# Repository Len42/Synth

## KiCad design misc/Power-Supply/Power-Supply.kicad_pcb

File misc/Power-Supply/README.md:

# Eurorack Power Supply

This is the power supply that I made for my Eurorack modular system.

[See here for more info, photos, etc.](https://lenp.net/synth/power-supply/)

### Specs

Input: Requires between 9 V and 36 V DC, 35W (from a power brick / wall wart / laptop charger)

Output: +12 V, -12 V (1 A each), +5 V (500 mA)

### Notes

I used an old laptop charger as the AC-DC converter (power brick) so I didn't have to mess around with mains voltage. The required Eurorack voltages (+12 V, -12 V, +5 V) are supplied by switching DC-DC converters. The outputs are isolated from the input.

There are two 16-pin Eurorack power connectors; you'll want a busboard or flying-bus cable to feed multiple modules.

The power supply is assembled on a stripboard PCB. I have provided a layout diagram.

Please note that I am a hobbyist, not a trained electronics engineer. No guarantees!

### Software Used

[KiCad](https://www.kicad.org/) 6.0.10

<hr /><br />© 2022 Len Popp CC BY<br />This work is licensed under a <a rel="license" href="http://creativecommons.org/licenses/by/4.0/">Creative Commons Attribution 4.0 International License</a>.

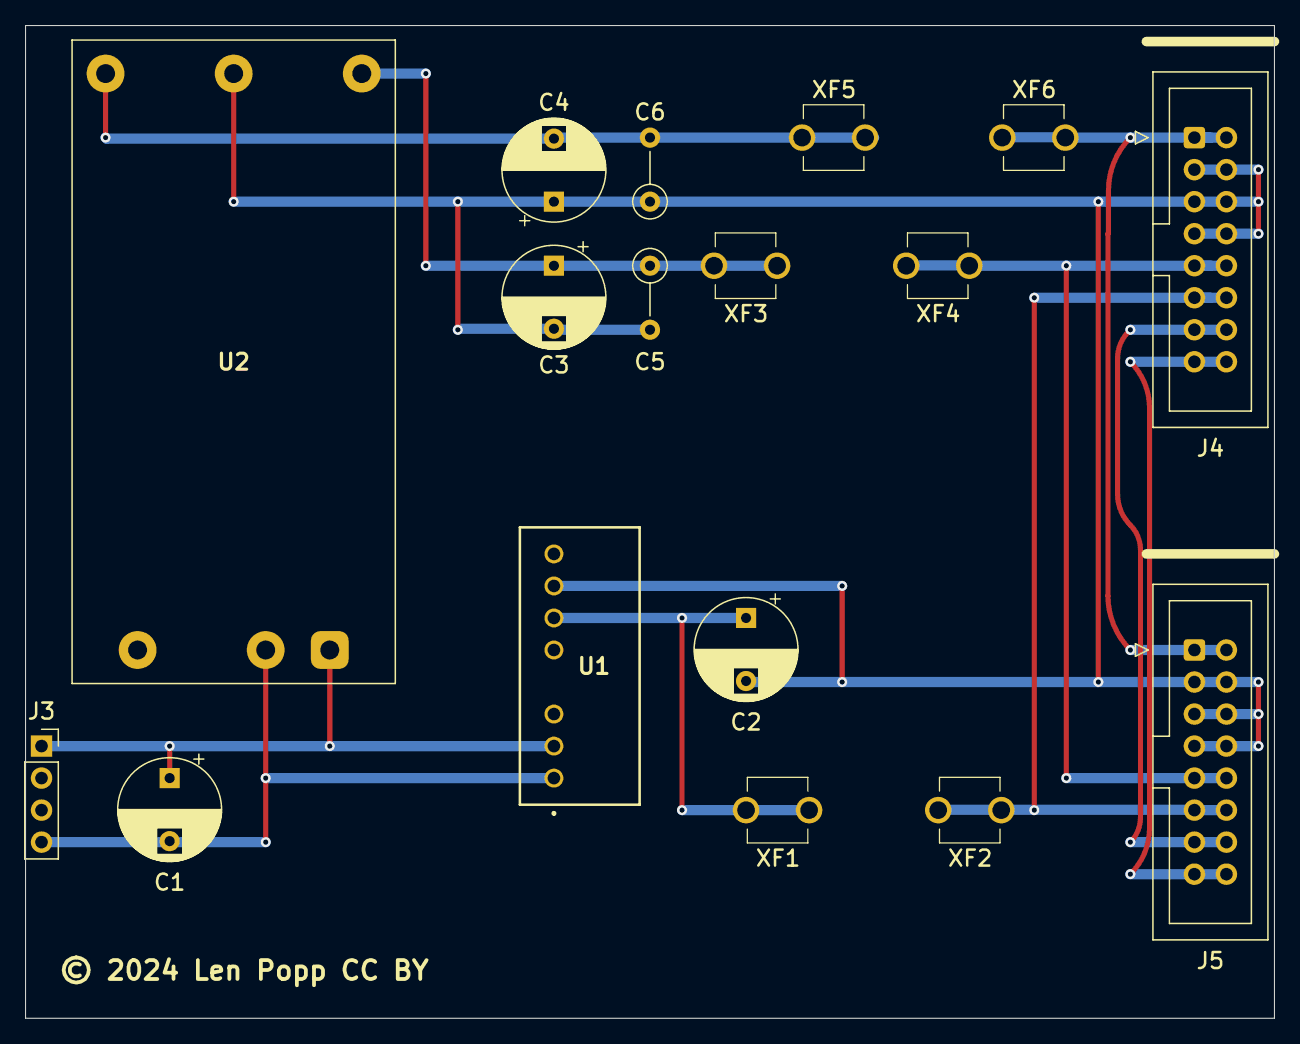
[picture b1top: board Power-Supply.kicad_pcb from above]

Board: 2 copper layers, 99.1 x 78.7 mm, 17 parts (0 on the bottom side), 11 nets.

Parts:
C1, C3, C4: 220U; CP_Radial_D8.0mm_P5.00mm
C2: 22U; CP_Radial_D8.0mm_P5.00mm
C5, C6: 100N; SB_Gen_2
J3: HDR_F; PinSocket_1x04_P2.54mm_Vertical
J4, J5: Conn_Eurorack_Pwr_16; IDC-Header-Eurorack-16-TH
U1: PRM3W-E12-S5-S; Converter_DCDC_CUI_PRM3W
U2: PYBE30-Q24-D12; Converter_DCDC_CUI_PYBE30
XF1, XF2, XF3, XF4, XF5, XF6: CLIP; FuseClip_D5mm_P5mm_52000001009

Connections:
+5V: J4.11 (+5V), J4.12, J5.11 (+5V), J5.12, XF2.1
+12V: J4.9 (+12V), J4.10, J5.9 (+12V), J5.10, XF4.1
-12V: J4.1 (-12V), J4.2, J5.1 (-12V), J5.2, XF6.1
GND: C2.2, C3.2, C4.1, C5.2, C6.1, J4.3 (GND), J4.4, J4.5 (GND), J4.6, J4.7 (GND), J4.8, J5.3 (GND), J5.4, J5.5 (GND), J5.6, J5.7 (GND), J5.8, U1.7 (0V), U2.5 (0V)
unnamed: C1.1, J3.1, U1.2 (+VIN), U2.1 (+VIN)
unnamed: C1.2, J3.4, U1.1 (-VIN), U2.2 (-VIN)
unnamed: C2.1, U1.6 (+VOUT), XF1.1
unnamed: C3.1, C5.1, U2.6 (+VOUT), XF3.1
unnamed: C4.2, C6.2, U2.4 (-VOUT), XF5.1
unnamed: J4.13 (CV), J4.14, J5.13 (CV), J5.14
unnamed: J4.15 (GATE), J4.16, J5.15 (GATE), J5.16

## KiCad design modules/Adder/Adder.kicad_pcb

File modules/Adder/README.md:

# Unity-Gain Mixer / Precision Adder

## 4HP Eurorack Module

### Features
- Two 3:1 mixing channels usable for CV or audio signals
- All inputs are mixed equally, _i.e._ added together
- Blinking lights show when an output is active and whether it's a CV or audio signal
- _Optional:_ A high-precision CV adder, if precision components are used

### Notes
To make a high-precision adder (_e.g._ to add pitch CVs without going out of tune):
- Use precision resistors (0.1% tolerance) for all 10kΩ resistors
- Use precision op-amps for U1, U2, and U4 (but not U3, all it does is blink an LED)

Note that some precision op-amps have low bandwidth or slew rate, which can be a problem for mixing audio signals. For example, I found that the LT1013/4 is good for accurately adding pitch CVs but causes distortion of audio-frequency signals. A possible compromise is to use precision resistors and regular op-amps (TL07x).

PCB layouts are provided in KiCad and gerber formats. A PCB layout for a drilled front panel (with no labels) is also included.

The PCBs that I used can be ordered from OSH Park. The designs are here:
- [Controls board](https://oshpark.com/shared_projects/eqKM6fyu)
- [Main board](https://oshpark.com/shared_projects/4ohHbdpn)
- [Front panel](https://oshpark.com/shared_projects/z20NA99Y)

Please note that I am a hobbyist, not a trained electronics engineer. No guarantees!

### Software Used

* [KiCad](https://www.kicad.org/) 6.0.8

<hr /><div><div style="float:left; padding-right:10px;"></div><div style="xfloat:left; padding-left:10px;"><br />© 2022 Len Popp CC BY<br />This work is licensed under a <a rel="license" href="http://creativecommons.org/licenses/by/4.0/">Creative Commons Attribution 4.0 International License</a>.</div></div>

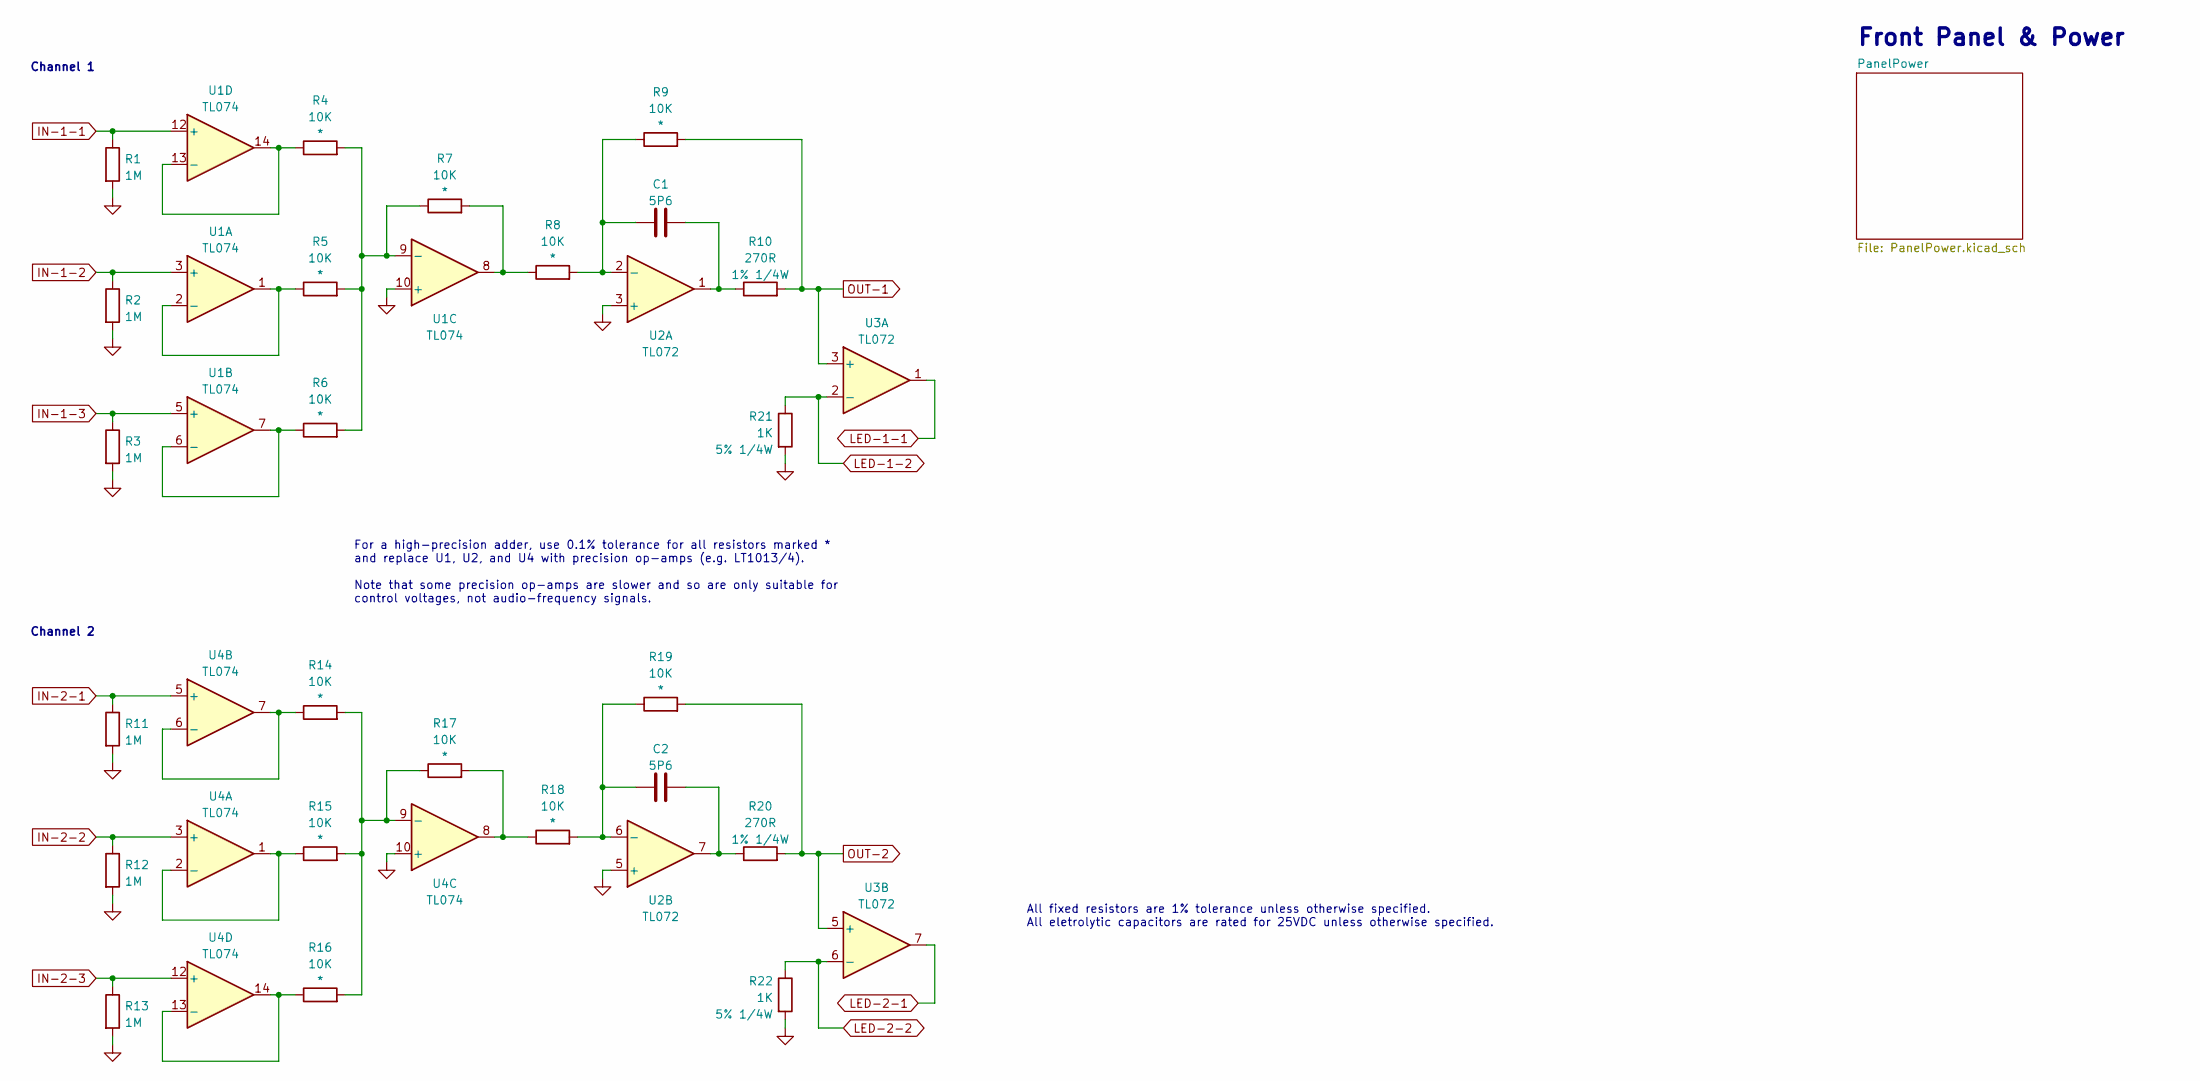
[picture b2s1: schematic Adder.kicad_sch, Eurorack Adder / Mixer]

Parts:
C1, C2: 5P6; C_Disc_D5.0mm_W2.5mm_P2.50mm; ManufacturerPartNum C315C569D1G5TA
R1, R2, R3, R11, R12, R13: 1M; R_Axial_DIN0207_L6.3mm_D2.5mm_P7.62mm_Horizontal; ManufacturerPartNum MFR-12FTF52-1M
R4, R5, R6, R7, R8, R9, R14, R15, R16, R17, R18, R19: 10K; R_Axial_DIN0207_L6.3mm_D2.5mm_P10.16mm_Horizontal; ManufacturerPartNum MFR-12FTF52-10K
R10, R20: 270R; R_Axial_DIN0207_L6.3mm_D2.5mm_P10.16mm_Horizontal; ManufacturerPartNum MFR-25FRF52-270R
R21, R22: 1K; R_Axial_DIN0207_L6.3mm_D2.5mm_P10.16mm_Horizontal; ManufacturerPartNum CCF071K00JKE36
U1, U4: TL074; DIP-14_W7.62mm; ManufacturerPartNum TL074BCN
U2, U3: TL072; DIP-8_W7.62mm; ManufacturerPartNum TL072BCP

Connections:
GND: R1.2, R2.2, R3.2, R11.2, R12.2, R13.2, R21.2, R22.2, U1.10 (+), U2.3 (+), U2.5 (+), U4.10 (+); also elsewhere on the board
IN-1-1: R1.1, U1.12 (+); also elsewhere on the board
IN-1-2: R2.1, U1.3 (+); also elsewhere on the board
IN-1-3: R3.1, U1.5 (+); also elsewhere on the board
IN-2-1: R11.1, U4.5 (+); also elsewhere on the board
IN-2-2: R12.1, U4.3 (+); also elsewhere on the board
IN-2-3: R13.1, U4.12 (+); also elsewhere on the board
LED-1-1: U3.1; also elsewhere on the board
LED-1-2: R21.1, U3.2 (-); also elsewhere on the board
LED-2-1: U3.7; also elsewhere on the board
LED-2-2: R22.1, U3.6 (-); also elsewhere on the board
unnamed: C1.1, R8.2, R9.1, U2.2 (-)
unnamed: C1.2, R10.1, U2.1
unnamed: C2.1, R18.2, R19.1, U2.6 (-)
unnamed: C2.2, R20.1, U2.7
unnamed: R4.1, U1.13 (-), U1.14
unnamed: R4.2, R5.2, R6.2, R7.1, U1.9 (-)
unnamed: R5.1, U1.1, U1.2 (-)
unnamed: R6.1, U1.6 (-), U1.7
unnamed: R7.2, R8.1, U1.8
unnamed: R14.1, U4.6 (-), U4.7
unnamed: R14.2, R15.2, R16.2, R17.1, U4.9 (-)
unnamed: R15.1, U4.1, U4.2 (-)
unnamed: R16.1, U4.13 (-), U4.14
unnamed: R17.2, R18.1, U4.8
OUT-1: R9.2, R10.2, U3.3 (+); also elsewhere on the board
OUT-2: R19.2, R20.2, U3.5 (+); also elsewhere on the board

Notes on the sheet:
All fixed resistors are 1% tolerance unless otherwise specified. All eletrolytic capacitors are rated for 25VDC unless otherwise specified.
For a high-precision adder, use 0.1% tolerance for all resistors marked * and replace U1, U2, and U4 with precision op-amps (e.g. LT1013/4). Note that some precision op-amps are slower and so are only suitable for control voltages, not audio-frequency signals.
Front Panel & Power
Channel 1
Channel 2

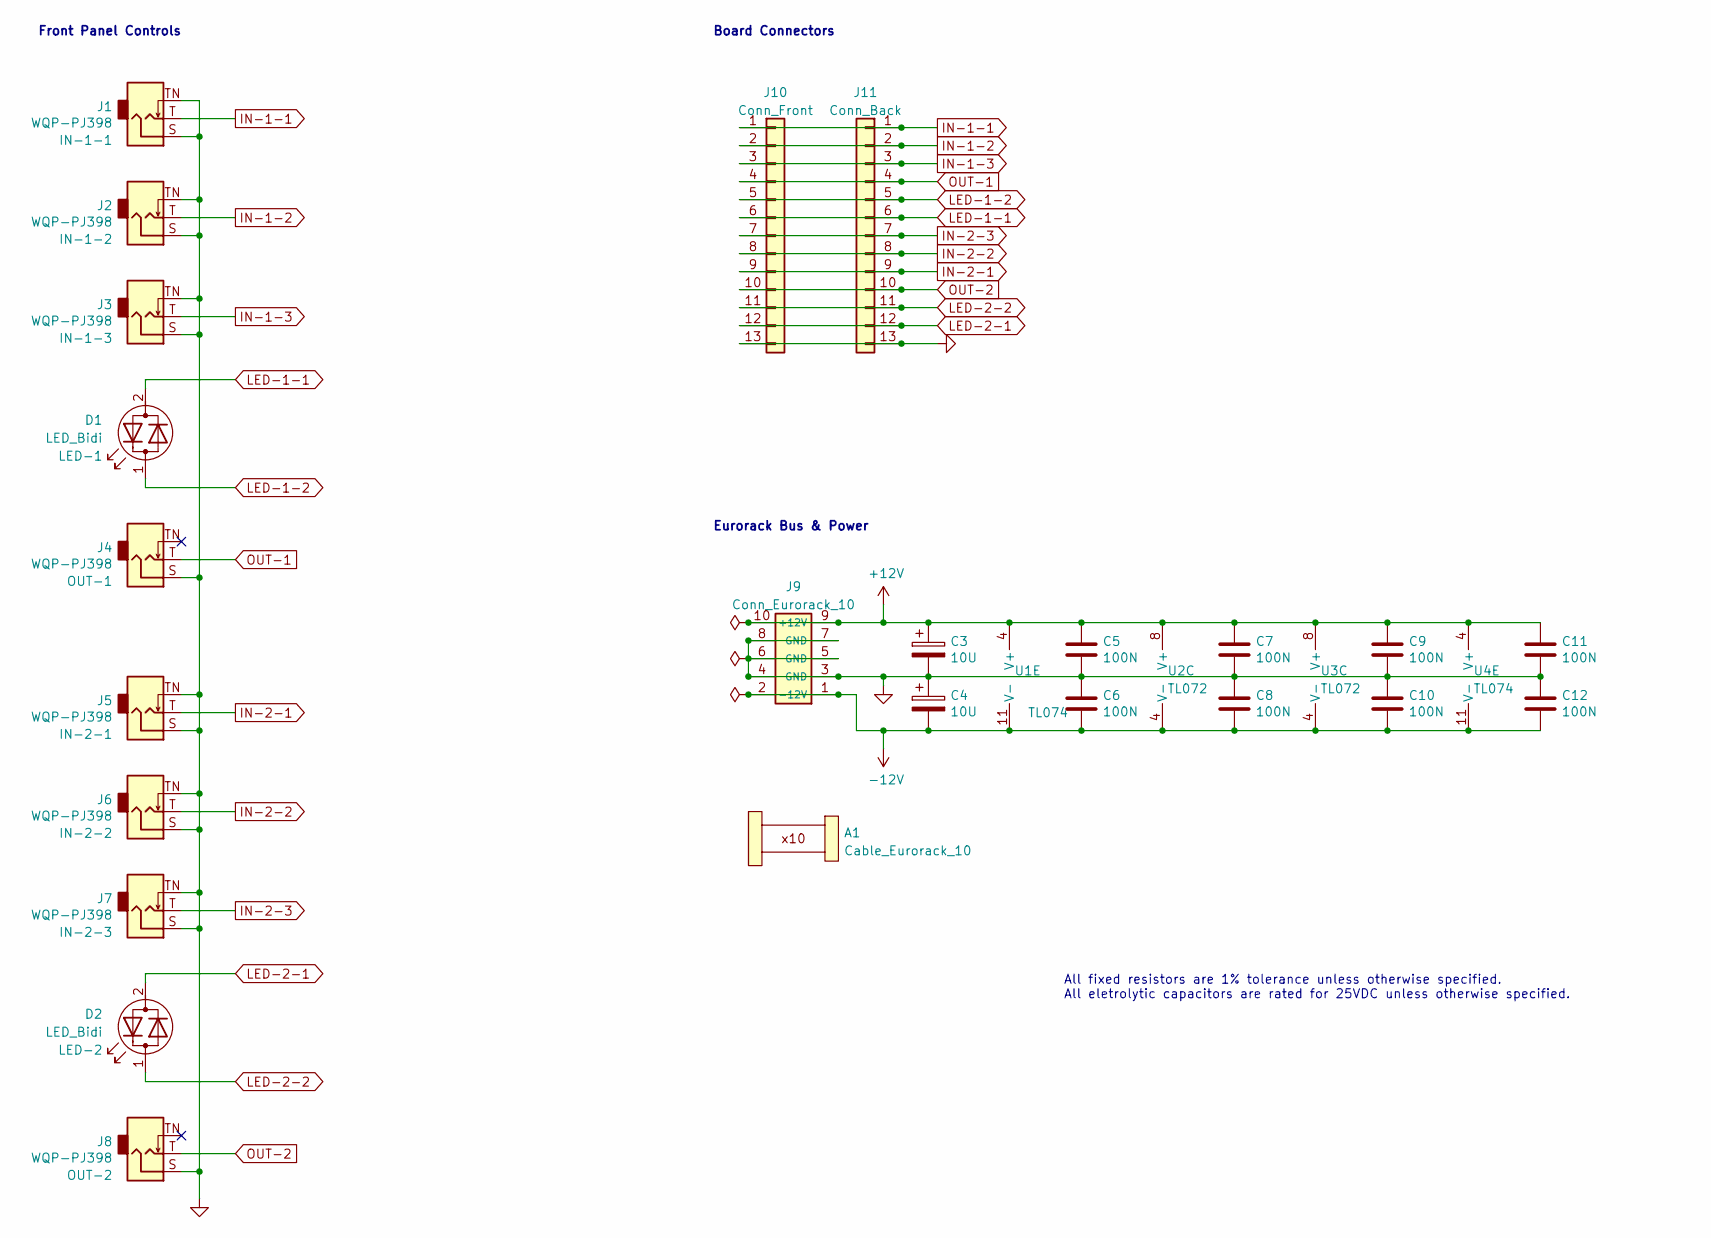
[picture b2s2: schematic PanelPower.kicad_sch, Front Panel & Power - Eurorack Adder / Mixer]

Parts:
A1: Cable_Eurorack_10; NoFootprint
C3, C4: 10U; CP_Radial_D5.0mm_P2.50mm; ManufacturerPartNum ECE-A1VKS100I
C5, C6, C7, C8, C9, C10, C11, C12: 100N; C_Disc_D5.0mm_W2.5mm_P2.50mm; ManufacturerPartNum FG18X7R1H104KNT06
D1, D2: LED_Bidi; LED_D3.0mm; ManufacturerPartNum WP937GYW
J1, J2, J3, J4, J5, J6, J7, J8: WQP-PJ398; Jack_3.5mm_QingPu_WQP-PJ398SM_Vertical; ManufacturerPartNum PJ398SM / WQP518MA
J9: Conn_Eurorack_10; IDC-Header-Eurorack-10-TH; ManufacturerPartNum 61201021621
J10: Conn_Front; PinSocket_1x13_P2.54mm_Vertical
J11: Conn_Back; PinHeader_1x13_P2.54mm_Horizontal
U1, U4: TL074; DIP-14_W7.62mm; ManufacturerPartNum TL074BCN
U2, U3: TL072; DIP-8_W7.62mm; ManufacturerPartNum TL072BCP

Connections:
+12V: C3.1, C5.1, C7.1, C9.1, C11.1, J9.9 (+12V), J9.10, U1.4 (V+), U2.8 (V+), U3.8 (V+), U4.4 (V+)
-12V: C4.2, C6.2, C8.2, C10.2, C12.2, J9.1 (-12V), J9.2, U1.11 (V-), U2.4 (V-), U3.4 (V-), U4.11 (V-)
GND: C3.2, C4.1, C5.2, C6.1, C7.2, C8.1, C9.2, C10.1, C11.2, C12.1, J1.S, J1.TN, J2.S, J2.TN, J3.S, J3.TN, J4.S, J5.S, J5.TN, J6.S, J6.TN, J7.S, J7.TN, J8.S, J9.3 (GND), J9.4, J9.5 (GND), J9.6, J9.7 (GND), J9.8, J10.13, J11.13; also elsewhere on the board
IN-1-1: J1.T, J10.1, J11.1; also elsewhere on the board
IN-1-2: J2.T, J10.2, J11.2; also elsewhere on the board
IN-1-3: J3.T, J10.3, J11.3; also elsewhere on the board
IN-2-1: J5.T, J10.9, J11.9; also elsewhere on the board
IN-2-2: J6.T, J10.8, J11.8; also elsewhere on the board
IN-2-3: J7.T, J10.7, J11.7; also elsewhere on the board
LED-1-1: D1.2, J10.6, J11.6; also elsewhere on the board
LED-1-2: D1.1, J10.5, J11.5; also elsewhere on the board
LED-2-1: D2.2, J10.12, J11.12; also elsewhere on the board
LED-2-2: D2.1, J10.11, J11.11; also elsewhere on the board
OUT-1: J4.T, J10.4, J11.4; also elsewhere on the board
OUT-2: J8.T, J10.10, J11.10; also elsewhere on the board

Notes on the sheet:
All fixed resistors are 1% tolerance unless otherwise specified. All eletrolytic capacitors are rated for 25VDC unless otherwise specified.
Eurorack Bus & Power
Board Connectors
Front Panel Controls

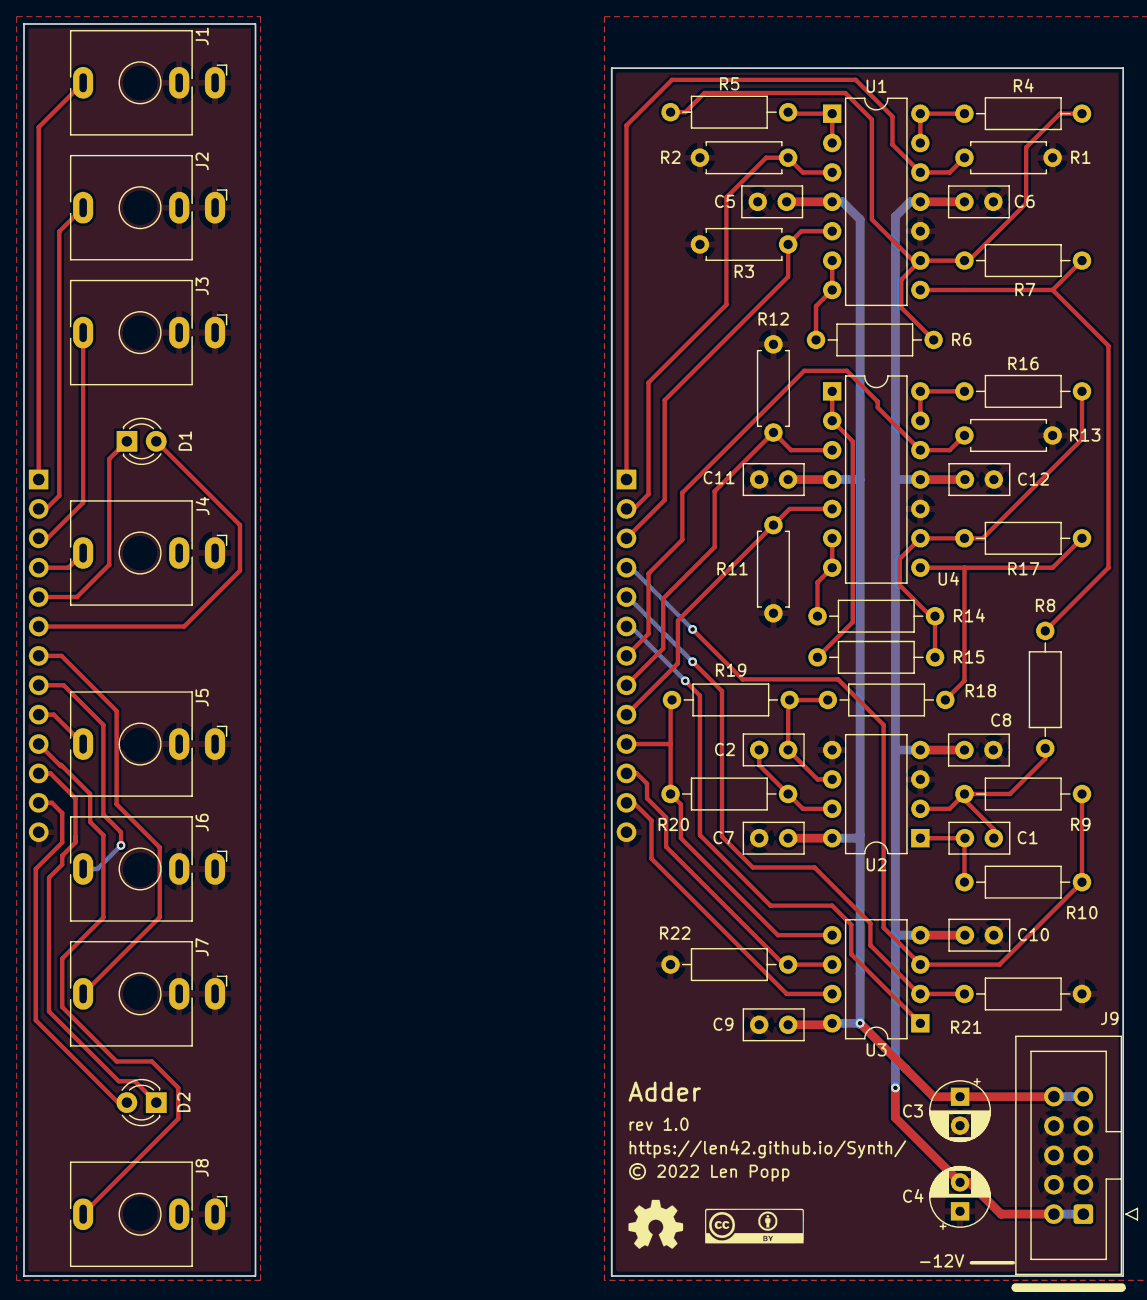
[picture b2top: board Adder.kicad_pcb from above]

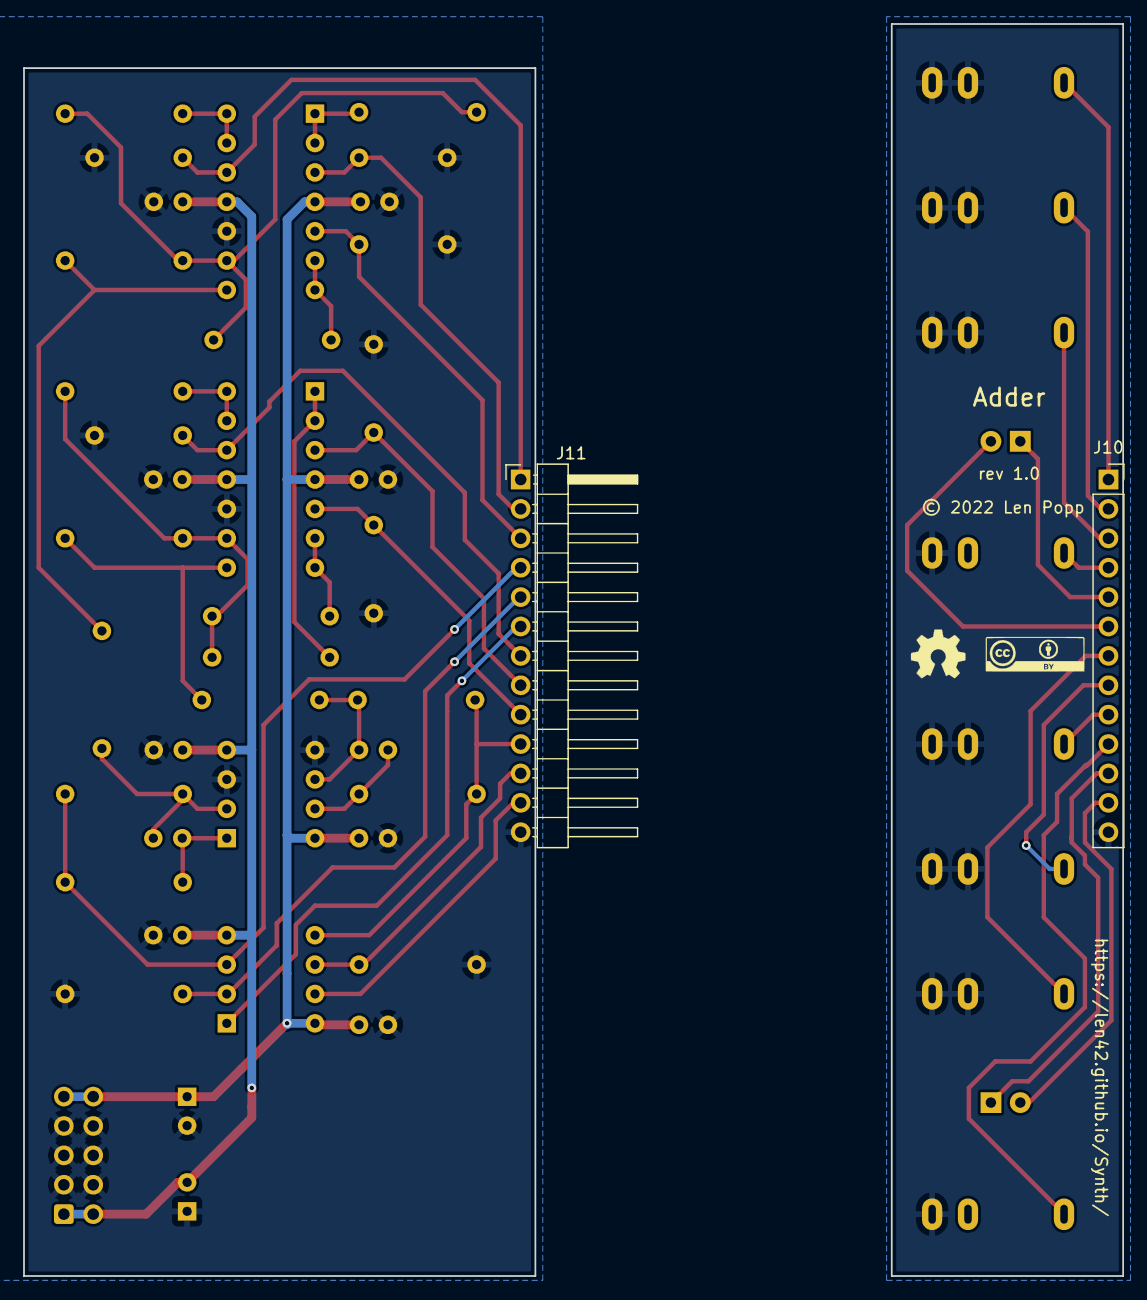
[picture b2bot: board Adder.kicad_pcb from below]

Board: 2 copper layers, 95.0 x 108.2 mm, 55 parts (4 on the bottom side), 29 nets.

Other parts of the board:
G1, G2: Logo_CC_BY
G3, G4: Logo_OSHW

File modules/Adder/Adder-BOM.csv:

Ref,Qty,Value,Value2,Note,Description,Datasheet,Manufacturer,ManuPartNum,Distributor1,DistributorPartNum1,DistributorPartLink1,Distributor2,DistributorPartNum2,DistributorPartLink2,Distributor3,DistributorPartNum3,DistributorPartLink3
"A1","1","Cable_Eurorack_10","","Length as required","Eurorack 16-10 pin power cable","","","","Thonk","","https://www.thonk.co.uk/shop/eurorack-power-cables/","SynthCube","","https://synthcube.com/cart/eurorack-ribbon-power-cables","Modular Addict","","https://modularaddict.com/parts/eurorack-power-cables-1"
"C1 C2","2","5P6","C0G/NP0","","Capacitor - Ceramic","https://www.mouser.ca/datasheet/2/212/KEM_C1049_GOLDMAX_C0G-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","KEMET","C315C569D1G5TA","Mouser","80-C315C569D1G","https://www.mouser.ca/ProductDetail/?qs=qe%2F8UmbcoTBh6wC284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","","","","","",""
"C3 C4","2","10U","35 VDC","12 V decoupling","Capacitor - Electrolytic - 12 V decoupling","https://www.mouser.ca/datasheet/2/315/ABA0000C1059-947582.pdf","Panasonic","ECE-A1VKS100I","Mouser","667-ECE-A1VKS100I","https://www.mouser.ca/ProductDetail/667-ECE-A1VKS100I","Thonk","Group_Eurorack_DIY_Essential","https://www.thonk.co.uk/shop/eurorack-diy-essentials/","","",""
"C5 C6 C7 C8 C9 C10 C11 C12","8","100N","","IC decoupling","Capacitor - Ceramic - IC decoupling","https://product.tdk.com/system/files/dam/doc/product/capacit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","TDK","FG18X7R1H104KNT06","Mouser","810-FG18X7R1H104KNT6","https://www.mouser.ca/ProductDetail/810-FG18X7R1H104KNT6","","","","","",""
"D1 D2","2","LED_Bidi","","","Dual LED, red and green, common cathode on pin 2","https://www.mouser.ca/datasheet/2/216/WP937GYW-49419.pdf","Kingbright","WP937GYW","Mouser","604-WP937GYW","https://www.mouser.ca/ProductDetail/Kingbright/WP937GYW?qs=p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","","","","","",""
"J1 J2 J3 J4 J5 J6 J7 J8","8","WQP-PJ398","","","Audio Jack, 2 Poles (Mono / TS), Switched T Pole (Normalling), QingPu / Thonkiconn","http://www.qingpu-electronics.com/en/products/WQP-PJ398SM-362.html","QingPu / Thonk","PJ398SM / WQP518MA","Thonk","PJ398SM","https://www.thonk.co.uk/shop/thonkiconn/","SynthCube","WQP518MA","https://synthcube.com/cart/3-5mm-euro-jacks","Adafruit","4031","https://www.adafruit.com/product/4031"
"J9","1","Conn_Eurorack_10","","","Eurorack 10-pin board power connector","https://www.mouser.ca/datasheet/2/445/61201021621-1717731.pdf","Wurth Elektronik","61201021621","Mouser","710-61201021621","https://www.mouser.ca/ProductDetail/Wurth-Elektronik/6120102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","Thonk","","https://www.thonk.co.uk/shop/eurorack-diy-essentials/","","",""
"J10","1","Conn_Front","","","Generic connector, single row, 01x13, script generated (kicad-library-utils/schlib/autogen/connector/)","","","","Adafruit","598","https://www.adafruit.com/product/598","Mouser","710-61303211821","https://www.mouser.ca/ProductDetail/Wurth-Elektronik/6130321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","","",""
"J11","1","Conn_Back","","","Generic connector, single row, 01x13, script generated (kicad-library-utils/schlib/autogen/connector/)","","","","Adafruit","1540","https://www.adafruit.com/product/1540","Mouser","649-1012937993601BLF","https://www.mouser.ca/ProductDetail/Amphenol-FCI/10129379-93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","","",""
"R1 R2 R3 R11 R12 R13","6","1M","1% 1/6W","","Resistor","https://www.mouser.ca/datasheet/2/447/Yageo_LR_MFR_1-1714151.pdf","YAGEO","MFR-12FTF52-1M","Mouser","603-MFR-12FTF52-1M","https://www.mouser.ca/ProductDetail/YAGEO/MFR-12FTF52-1M?qs=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","","","","","",""
"R4 R5 R6 R7 R8 R9 R14 R15 R16 R17 R18 R19","12","10K","*","May use 0.1% instead","Resistor","https://www.mouser.ca/datasheet/2/447/Yageo_LR_MFR_1-1714151.pdf","YAGEO","MFR-12FTF52-10K","Mouser","603-MFR-12FTF52-10K","https://www.mouser.ca/ProductDetail/YAGEO/MFR-12FTF52-10K?qs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","","","","","",""
"R10 R20","2","270R","1% 1/4W","Output limiting","Resistor","https://www.mouser.ca/datasheet/2/447/Yageo_LR_MFR_1-1714151.pdf","YAGEO","MFR-25FRF52-270R","Mouser","603-MFR-25FRF52-270R","https://www.mouser.ca/ProductDetail/603-MFR-25FRF52-270R","","","","","",""
"R21 R22","2","1K","5% 1/4W","","Resistor","https://www.mouser.ca/datasheet/2/427/ccf07-1762725.pdf","Vishay / Dale","CCF071K00JKE36","Mouser","71-CCF071K00JKE36","https://www.mouser.ca/ProductDetail/Vishay-Dale/CCF071K00JKE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","","","","","",""
"U1 U4","2","TL074","","May use a precision opamp","Quad Low-Noise JFET-Input Operational Amplifiers, DIP-14/SOIC-14","http://www.ti.com/lit/ds/symlink/tl071.pdf","Texas Instruments","TL074BCN","Mouser","595-TL074BCN","https://www.mouser.ca/ProductDetail/?qs=vxEfx8VrU7BHurOY5iQd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","","","","","",""
"U2","1","TL072","","May use a precision opamp","Dual Low-Noise JFET-Input Operational Amplifiers, DIP-8/SOIC-8","https://www.ti.com/lit/ds/symlink/tl072b.pdf?ts=1628812694194","Texas Instruments","TL072BCP","Mouser","595-TL072BCP","https://www.mouser.ca/ProductDetail/Texas-Instruments/TL072B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","Mouser","584-LT1013DN8#PBF","https://www.mouser.ca/ProductDetail/Analog-Devices/LT1013DN8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","","",""
"U3","1","TL072","","","Dual Low-Noise JFET-Input Operational Amplifiers, DIP-8/SOIC-8","https://www.ti.com/lit/ds/symlink/tl072b.pdf?ts=1628812694194","Texas Instruments","TL072BCP","Mouser","595-TL072BCP","https://www.mouser.ca/ProductDetail/Texas-Instruments/TL072B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","","","","","",""

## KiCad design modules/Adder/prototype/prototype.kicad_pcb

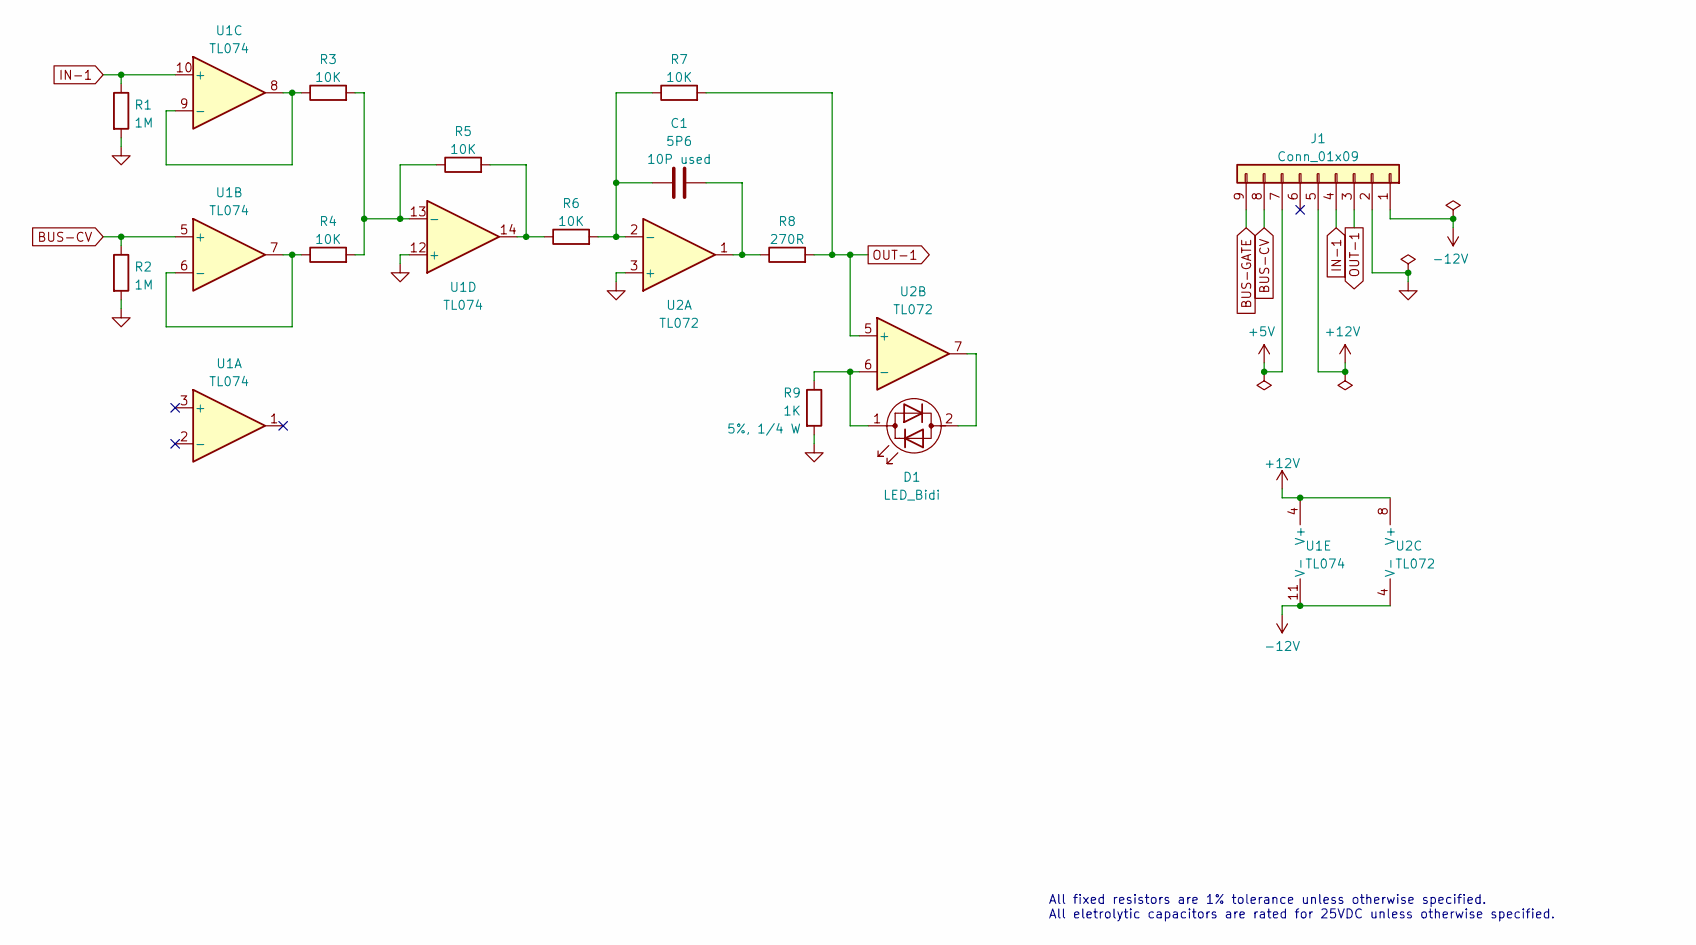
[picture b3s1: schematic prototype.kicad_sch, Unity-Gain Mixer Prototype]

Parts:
C1: 5P6; C_Disc_D5.0mm_W2.5mm_P2.50mm
D1: LED_Bidi; LED_D3.0mm; ManufacturerPartNum WP937GYW
J1: Conn_01x09; PinHeader_1x09_P2.54mm_Vertical
R1, R2: 1M; SB_Gen_1; ManufacturerPartNum MFR-12*
R3, R4, R6: 10K; R_Axial_DIN0207_L6.3mm_D2.5mm_P7.62mm_Horizontal; ManufacturerPartNum MFR-12*
R5: 10K; SB_Gen_1; ManufacturerPartNum MFR-12*
R7: 10K; SB_Gen_4; ManufacturerPartNum MFR-12*
R8: 270R; R_Axial_DIN0207_L6.3mm_D2.5mm_P7.62mm_Horizontal; ManufacturerPartNum MFR-12*
R9: 1K; SB_Gen_1; ManufacturerPartNum CCF071K00JKE36
U1: TL074; DIP-14_W7.62mm; ManufacturerPartNum TL074BCN
U2: TL072; DIP-8_W7.62mm; ManufacturerPartNum TL072BCP

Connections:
+5V: J1.7
+12V: J1.5, U1.4 (V+), U2.8 (V+)
-12V: J1.1, U1.11 (V-), U2.4 (V-)
BUS-CV: J1.8, R2.1, U1.5 (+)
BUS-GATE: J1.9
GND: J1.2, R1.2, R2.2, R9.2, U1.12 (+), U2.3 (+)
IN-1: J1.4, R1.1, U1.10 (+)
unnamed: C1.1, R6.2, R7.1, U2.2 (-)
unnamed: C1.2, R8.1, U2.1
unnamed: D1.1, R9.1, U2.6 (-)
unnamed: D1.2, U2.7
unnamed: R3.1, U1.8, U1.9 (-)
unnamed: R3.2, R4.2, R5.1, U1.13 (-)
unnamed: R4.1, U1.6 (-), U1.7
unnamed: R5.2, R6.1, U1.14
OUT-1: J1.3, R7.2, R8.2, U2.5 (+)

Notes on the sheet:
All fixed resistors are 1% tolerance unless otherwise specified. All eletrolytic capacitors are rated for 25VDC unless otherwise specified.

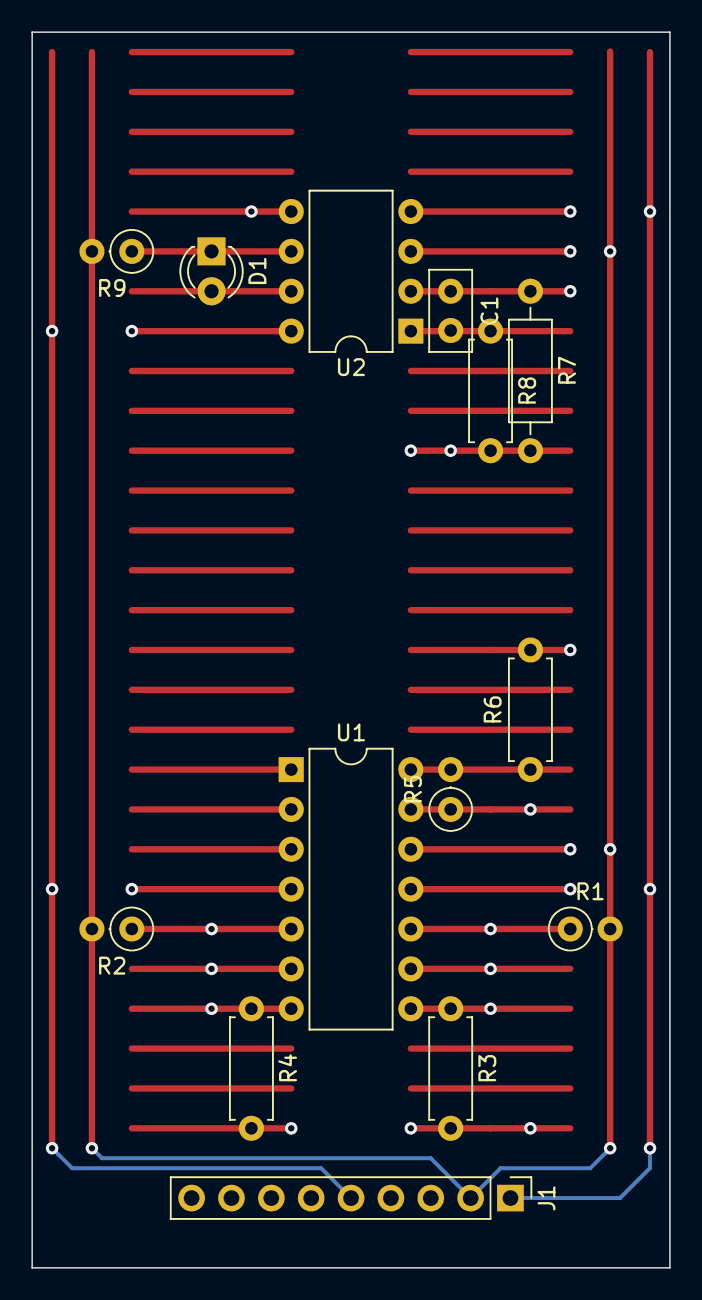
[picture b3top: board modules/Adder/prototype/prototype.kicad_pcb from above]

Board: 6 copper layers, 40.6 x 78.7 mm, 14 parts (0 on the bottom side), 14 nets.

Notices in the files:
misc/Power-Supply/Power-Supply.kicad_pcb:
Copyright © 2024 Len Popp CC BY
modules/Adder/Adder.kicad_pcb:
Copyright © 2022 Len Popp CC BY
modules/Audiout/Audiout.kicad_pcb:
© 2021 Len Popp
modules/Filter2/PanelPower.kicad_sch:
Copyright © 2023 Len Popp CC BY
